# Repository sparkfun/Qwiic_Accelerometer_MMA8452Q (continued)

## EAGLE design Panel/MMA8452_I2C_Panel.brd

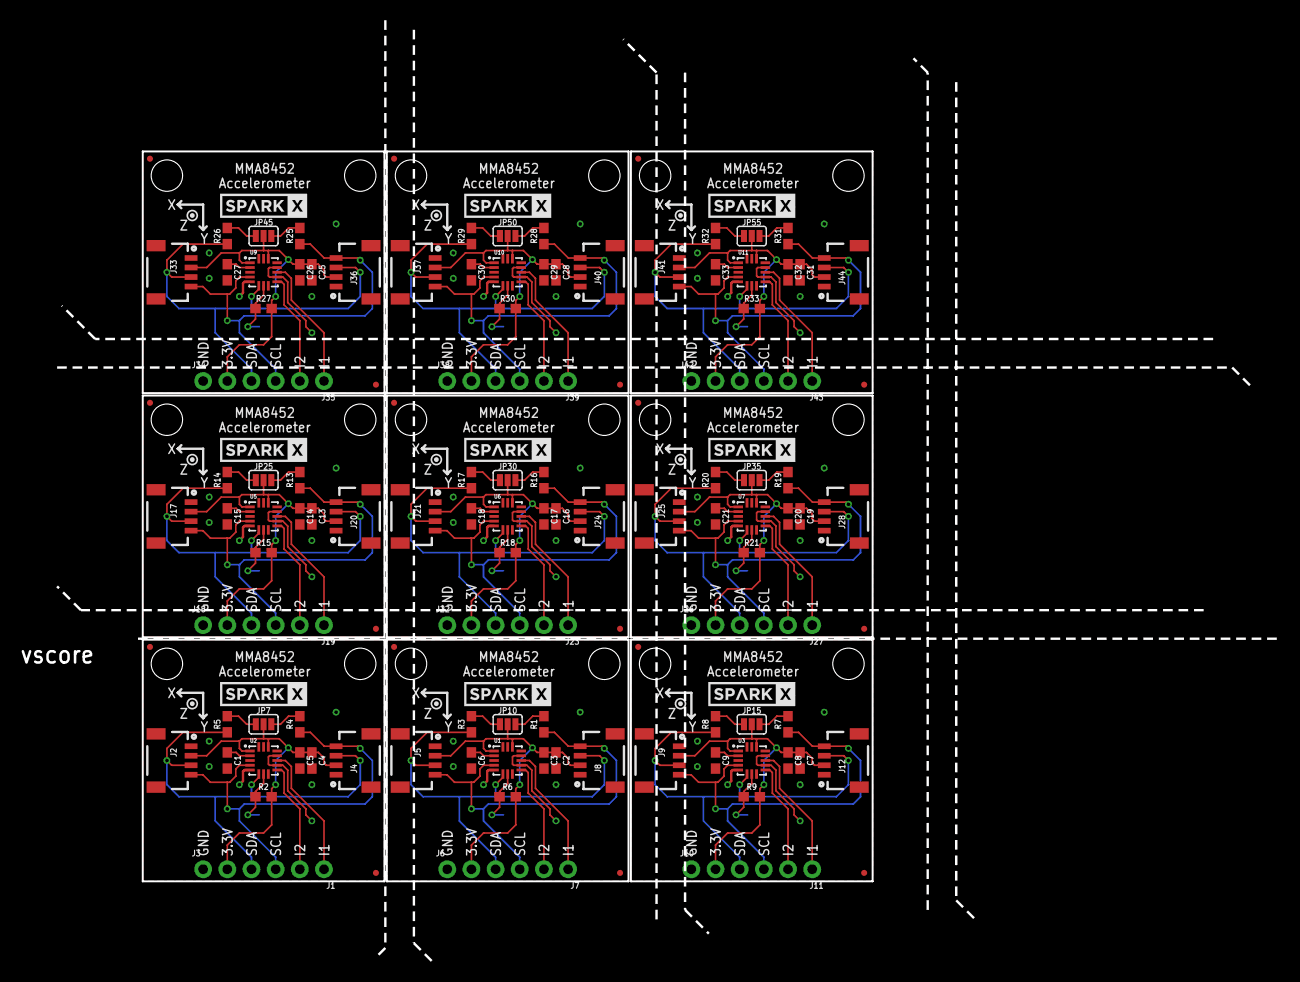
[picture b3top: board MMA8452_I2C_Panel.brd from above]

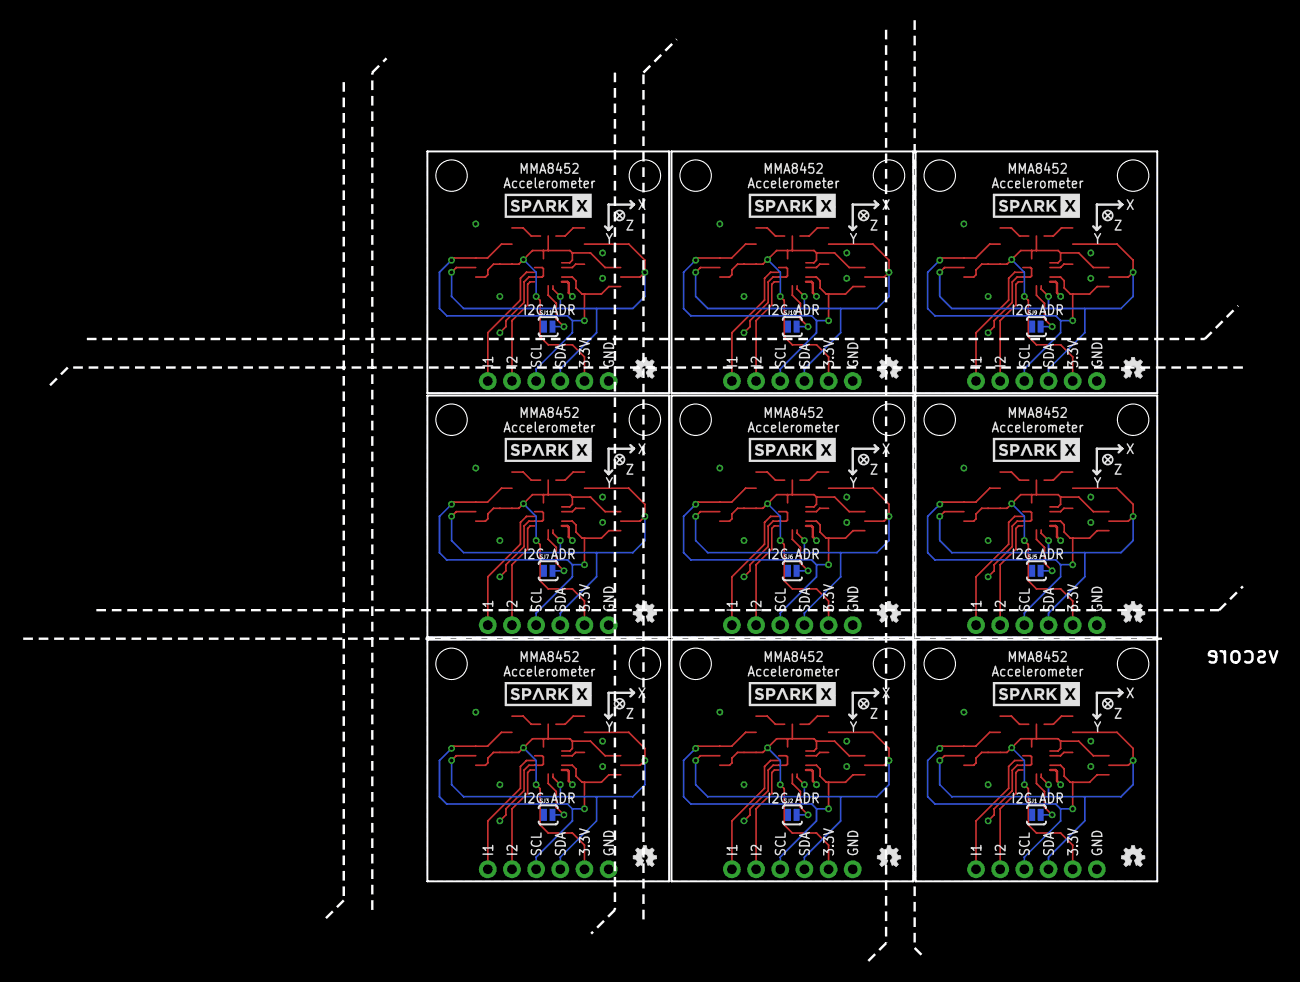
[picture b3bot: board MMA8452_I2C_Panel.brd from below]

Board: 2 copper layers, 128.5 x 99.0 mm, 180 parts (27 on the bottom side), 90 nets.

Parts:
C1, C2, C4, C6, C7, C9, C13, C15, C16, C18, C19, C21, C25, C27, C28, C30, C31, C33: 0.1uF; 0603
C3, C5, C8, C14, C17, C20, C26, C29, C32: 4.7uF; 0603
J1, J7, J11, J19, J23, J27, J35, J39, J43: 1X02_NO_SILK
J2, J4, J5, J8, J9, J12, J17, J20, J21, J24, J25, J28, J33, J36, J37, J40, J41, J44: SMD; 1X04_1MM_RA
J3, J6, J10, J18, J22, J26, J34, J38, J42: PTH; 1X04_NO_SILK
JP1, JP3, JP4, JP5, JP11, JP12, JP21, JP22, JP26, JP27, JP31, JP32, JP41, JP42, JP46, JP47, JP51, JP52: STAND-OFF
JP2, JP6, JP8, JP9, JP13, JP14, JP23, JP24, JP28, JP29, JP33, JP34, JP43, JP44, JP48, JP49, JP53, JP54: FIDUCIALUFIDUCIAL; MICRO-FIDUCIAL
JP7, JP10, JP15, JP25, JP30, JP35, JP45, JP50, JP55: SMT-JUMPER_3_2-NC_PASTE_SILK
LOGO1, LOGO2, LOGO3, LOGO5, LOGO6, LOGO7, LOGO9, LOGO10, LOGO11: OSHW-LOGOMINI; OSHW-LOGO-MINI
R1, R3, R4, R5, R7, R8, R13, R14, R16, R17, R19, R20, R25, R26, R28, R29, R31, R32: 4.7k; 0603
R2, R6, R9, R15, R18, R21, R27, R30, R33: 10k; 0603
SJ1, SJ2, SJ3, SJ5, SJ6, SJ7, SJ9, SJ10, SJ11: SJ_2S-NO
U1, U2, U3, U5, U6, U7, U9, U10, U11: MMA8452Q; QFN-16_0.5MM
U$1, U$2, U$3, U$4, U$5, U$6, U$9, U$10, U$11, U$12, U$13, U$14, U$17, U$18, U$19, U$20, U$21, U$22: SPARKX-LOGO4; SPARKX-MEDIUM

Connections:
3.3V: C4.1, C5.1, J2.2, J3.2, J4.2, JP7.2, R2.2, U2.1, U2.14
3.3V1: C2.1, C3.1, J5.2, J6.2, J8.2, JP10.2, R6.2, U1.1, U1.14
3.3V2: C7.1, C8.1, J9.2, J10.2, J12.2, JP15.2, R9.2, U3.1, U3.14
3.3V4: C13.1, C14.1, J17.2, J18.2, J20.2, JP25.2, R15.2, U5.1, U5.14
3.3V5: C16.1, C17.1, J21.2, J22.2, J24.2, JP30.2, R18.2, U6.1, U6.14
3.3V6: C19.1, C20.1, J25.2, J26.2, J28.2, JP35.2, R21.2, U7.1, U7.14
3.3V8: C25.1, C26.1, J33.2, J34.2, J36.2, JP45.2, R27.2, U9.1, U9.14
3.3V9: C28.1, C29.1, J37.2, J38.2, J40.2, JP50.2, R30.2, U10.1, U10.14
3.3V10: C31.1, C32.1, J41.2, J42.2, J44.2, JP55.2, R33.2, U11.1, U11.14
BYP: C1.1, U2.2
BYP1: C6.1, U1.2
BYP2: C9.1, U3.2
BYP4: C15.1, U5.2
BYP5: C18.1, U6.2
BYP6: C21.1, U7.2
BYP8: C27.1, U9.2
BYP9: C30.1, U10.2
BYP10: C33.1, U11.2
GND: C1.2, C4.2, C5.2, J2.1, J3.1, J4.1, SJ1.1, U2.5, U2.10, U2.12
GND1: C2.2, C3.2, C6.2, J5.1, J6.1, J8.1, SJ2.1, U1.5, U1.10, U1.12
GND2: C7.2, C8.2, C9.2, J9.1, J10.1, J12.1, SJ3.1, U3.5, U3.10, U3.12
GND4: C13.2, C14.2, C15.2, J17.1, J18.1, J20.1, SJ5.1, U5.5, U5.10, U5.12
GND5: C16.2, C17.2, C18.2, J21.1, J22.1, J24.1, SJ6.1, U6.5, U6.10, U6.12
GND6: C19.2, C20.2, C21.2, J25.1, J26.1, J28.1, SJ7.1, U7.5, U7.10, U7.12
GND8: C25.2, C26.2, C27.2, J33.1, J34.1, J36.1, SJ9.1, U9.5, U9.10, U9.12
GND9: C28.2, C29.2, C30.2, J37.1, J38.1, J40.1, SJ10.1, U10.5, U10.10, U10.12
GND10: C31.2, C32.2, C33.2, J41.1, J42.1, J44.1, SJ11.1, U11.5, U11.10, U11.12
INT1: J1.1, U2.11
INT2: J1.2, U2.9
INT3: J7.2, U1.9
INT4: J7.1, U1.11
INT5: J11.2, U3.9
INT6: J11.1, U3.11
INT9: J19.2, U5.9
INT10: J19.1, U5.11
INT11: J23.2, U6.9
INT12: J23.1, U6.11
INT13: J27.2, U7.9
INT14: J27.1, U7.11
INT17: J35.2, U9.9
INT18: J35.1, U9.11
INT19: J39.2, U10.9
INT20: J39.1, U10.11
INT21: J43.2, U11.9
INT22: J43.1, U11.11
unnamed: JP7.1, R5.2
unnamed: JP7.3, R4.2
unnamed: JP10.1, R3.2
unnamed: JP10.3, R1.2
unnamed: JP15.1, R8.2
unnamed: JP15.3, R7.2
unnamed: JP25.1, R14.2
unnamed: JP25.3, R13.2
unnamed: JP30.1, R17.2
unnamed: JP30.3, R16.2
unnamed: JP35.1, R20.2
unnamed: JP35.3, R19.2
unnamed: JP45.1, R26.2
unnamed: JP45.3, R25.2
unnamed: JP50.1, R29.2
unnamed: JP50.3, R28.2
unnamed: JP55.1, R32.2
unnamed: JP55.3, R31.2
SA0: R2.1, SJ1.2, U2.7
SA1: R6.1, SJ2.2, U1.7
SA2: R9.1, SJ3.2, U3.7
SA4: R15.1, SJ5.2, U5.7
SA5: R18.1, SJ6.2, U6.7
SA6: R21.1, SJ7.2, U7.7
SA8: R27.1, SJ9.2, U9.7
SA9: R30.1, SJ10.2, U10.7
SA10: R33.1, SJ11.2, U11.7
SCL: J2.4, J3.4, J4.4, R4.1, U2.4
SCL1: J5.4, J6.4, J8.4, R1.1, U1.4
SCL2: J9.4, J10.4, J12.4, R7.1, U3.4
SCL4: J17.4, J18.4, J20.4, R13.1, U5.4
SCL5: J21.4, J22.4, J24.4, R16.1, U6.4
SCL6: J25.4, J26.4, J28.4, R19.1, U7.4
SCL8: J33.4, J34.4, J36.4, R25.1, U9.4
SCL9: J37.4, J38.4, J40.4, R28.1, U10.4
SCL10: J41.4, J42.4, J44.4, R31.1, U11.4
SDA: J2.3, J3.3, J4.3, R5.1, U2.6
SDA1: J5.3, J6.3, J8.3, R3.1, U1.6
SDA2: J9.3, J10.3, J12.3, R8.1, U3.6
SDA4: J17.3, J18.3, J20.3, R14.1, U5.6
SDA5: J21.3, J22.3, J24.3, R17.1, U6.6
SDA6: J25.3, J26.3, J28.3, R20.1, U7.6
SDA8: J33.3, J34.3, J36.3, R26.1, U9.6
SDA9: J37.3, J38.3, J40.3, R29.1, U10.6
SDA10: J41.3, J42.3, J44.3, R32.1, U11.6

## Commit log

2018-01-22 updated board to include address
2018-01-24 post design review changes
2018-01-24 Updated version number
2018-02-01 panel
2018-04-05 Updating README
2018-04-05 updated photo
